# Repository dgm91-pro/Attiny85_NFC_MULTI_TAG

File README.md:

# NFC Profile Keychain

See [`HACKCLUB_REQUEST.md`](HACKCLUB_REQUEST.md) for the message prepared for Hack Club.

A compact, battery-powered NFC keychain built around an **ATtiny85V** and an **ST25DV04KC dynamic NFC tag**. A single button switches between four configurable URL profiles, each indicated by an RGB LED.

> **Project status:** Prototype / under development. The firmware and hardware have not yet been independently verified. Please review the design and test it before relying on it.

## Features

- Four selectable NFC URL profiles: blue, red, green, and violet
- One-button interface
- RGB LED feedback
- NFC is disabled when the device starts and when it is switched off
- Selected profile is saved in the ATtiny85 EEPROM
- Low-power sleep while switched off
- I²C error feedback: four yellow flashes

## How it works

| Action | Result |
|---|---|
| Power-on | The keychain starts with NFC disabled |
| Short press while off | Enables NFC and displays the saved profile |
| Short press while on | Switches to the next profile: blue → red → green → violet |
| Long press (at least 1 second) while on | Disables NFC |
| While on | Brief LED pulse approximately every 4 seconds |
| I²C / NFC error | Four yellow flashes |

The four URL values are currently examples and should be replaced with the intended destinations before testing:

- `URL_0`: blue profile
- `URL_1`: red profile
- `URL_2`: green profile
- `URL_3`: violet profile

The firmware supports `http://` and `https://` URLs and documents a maximum URL length of 116 characters.

## Hardware

The current bill of materials includes:

- **Microcontroller:** ATtiny85V-10SU, 8-pin SOIC
- **NFC tag IC:** ST25DV04KC
- **RGB LED:** Kingbright APTF1616LSEEZGKQBKC, common anode
- **Battery:** CR2032 (3 V)
- **Button:** momentary tactile switch
- Supporting resistors and capacitors

The KiCad project files and a DigiKey parts-list CSV are included in this repository.

## Pin mapping

The mapping below follows the firmware comments and refers to the ATtiny85 SOIC-8 package pin numbers.

| ATtiny85 pin | Signal | Connection |
|---|---|---|
| 1 / PB5 | RESET | ISP header; 10 kΩ pull-up |
| 2 / PB3 | LED green | RGB LED cathode through resistor |
| 3 / PB4 | LED blue | RGB LED cathode through resistor |
| 4 | GND | Ground |
| 5 / PB0 | SDA | ST25DV04KC SDA; 10 kΩ pull-up |
| 6 / PB1 | LED red | RGB LED cathode through resistor |
| 7 / PB2 | SCL / button | ST25DV04KC SCL, 10 kΩ pull-up, button to GND |
| 8 | VCC | 3 V supply |

**Important:** PB2 is shared by I²C SCL and the button. The firmware waits for the button to be released before starting I²C operations.

## Firmware setup

The firmware is in [`program/program.ino`](program/program.ino).

1. Install Arduino IDE 2.x.
2. Install **ATTinyCore** and select the ATtiny85 target.
3. Select the **ATtiny85 (no bootloader)** board option and the internal 1 MHz clock.
4. Select a compatible ISP programmer, such as USBasp. The original notes specify the programmer's **SLOW** setting for a 1 MHz target.
5. Burn the bootloader / initialization sequence once to configure the fuses, if required by your setup.
6. Replace the example URLs in `program.ino`.
7. Remove the CR2032 before programming. Power the board from a suitable programmer or regulated supply set to the correct voltage, and upload using **Sketch → Upload Using Programmer**.

Menu labels can vary with Arduino IDE and ATTinyCore versions; confirm the target, clock, and fuse settings for your exact setup.

## Safety and testing notes

- **Remove the CR2032 before connecting a programmer or external power supply.** Never connect a battery to an external supply at the same time.
- Keep all programming signals within the ATtiny85's and NFC IC's supported voltage limits. Do not apply 5 V logic to a circuit designed for a 3 V supply.
- Verify the schematic, PCB footprint assignments, power connections, pull-ups, and LED polarity before assembling the board.
- Test the NFC behavior with a compatible NFC phone or reader and confirm that each profile opens the expected URL.
- The current repository has not been confirmed to compile or to work on physical hardware. A review and hardware test are still needed.

## Repository layout

```text
.
├── Budget/
│   ├── HackClub-8pin.csv
│   └── OSH-Park.png
├── KiCad/
│   ├── tag.zip
│   └── IF LIB NOT WORKING.zip
├── program/
│   └── program.ino
├── README.md
└── HACKCLUB_REQUEST.md
```

## Help / review requested

I would appreciate a quick review of the KiCad design and firmware before ordering or assembling the boards. In particular, I would like confirmation that the PCB and component footprints look correct, the ATtiny85/ST25DV04KC wiring is plausible, and the firmware's NFC/I²C behavior is likely to work as intended.

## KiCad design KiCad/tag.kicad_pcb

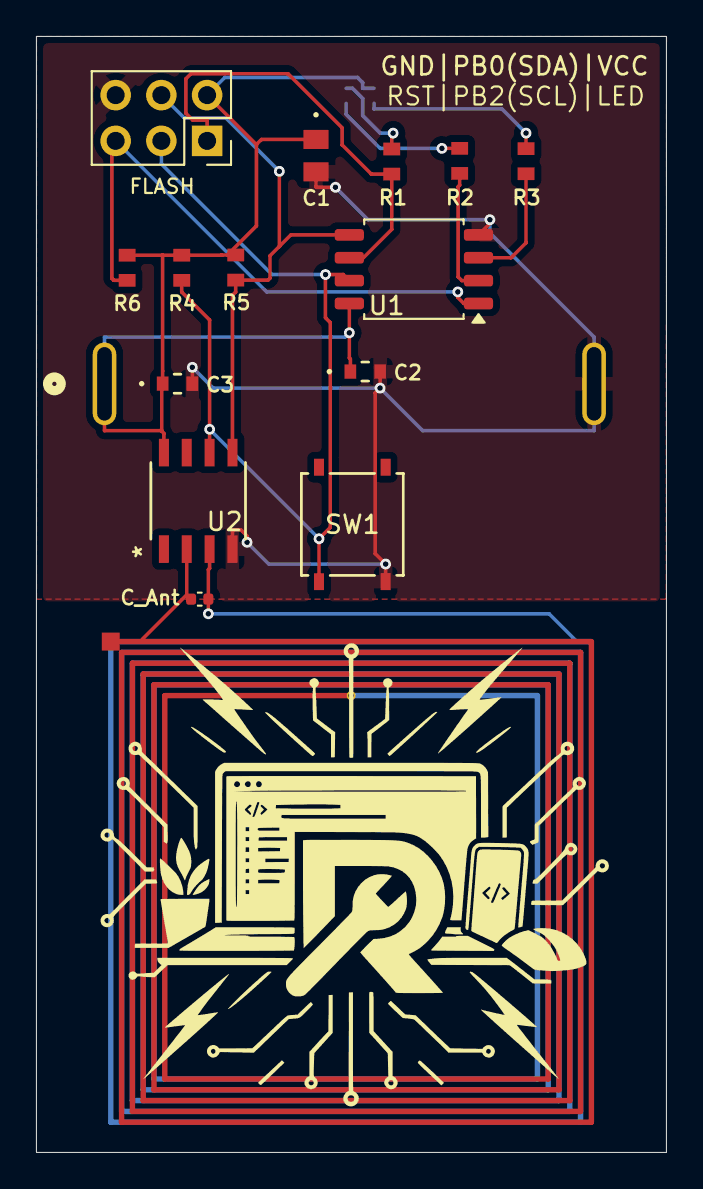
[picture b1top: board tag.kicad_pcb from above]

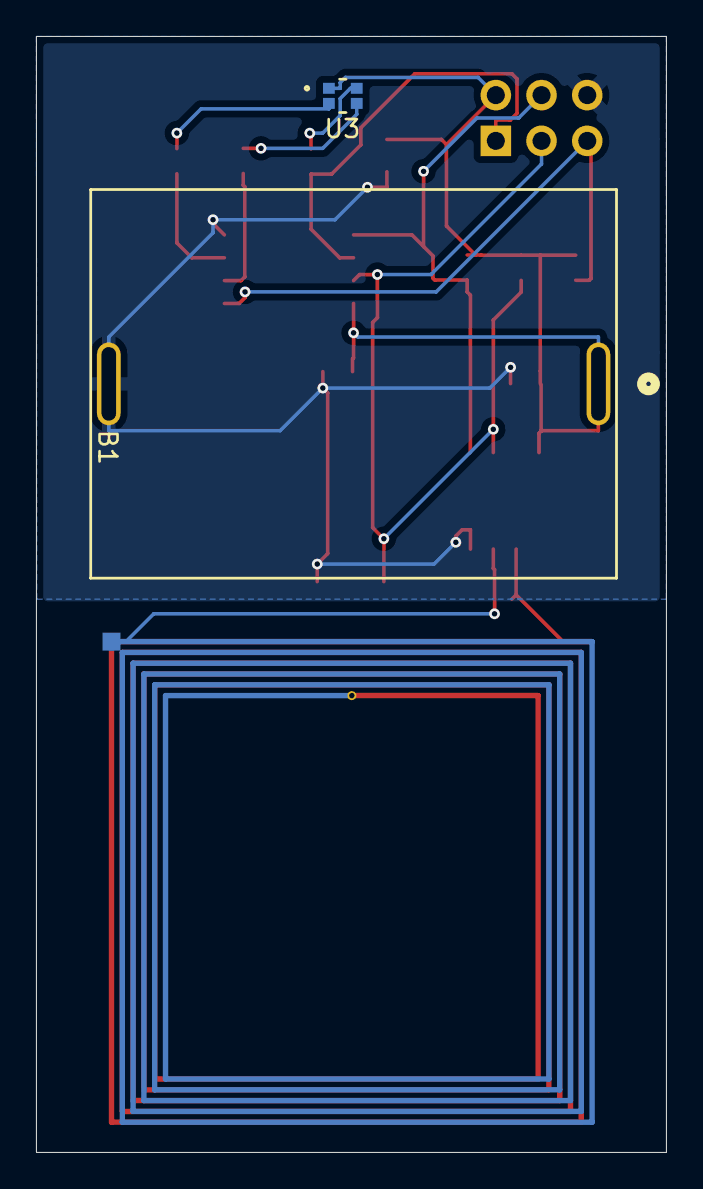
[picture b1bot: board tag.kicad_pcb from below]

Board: 2 copper layers, 35.0 x 62.0 mm, 17 parts (2 on the bottom side), 13 nets.

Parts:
B1: BC2032-E2; BC2032-E2_MPD
C1: CL21B106KOQNNNE; CAP_CL21B106KOQNNNE_SAM
C2, C3: CL10B104KO8NNNC; CAP_CL10_SAM
C_Ant: C; C_0402_1005Metric
FLASH: Conn_02x03_Counter_Clockwise; PinSocket_2x03_P2.54mm_Vertical
L1: L; ANT_Spiral_v3
R1: RMCF0603FT470R; STA_RMCF0603_STP
R2: RMCF0603FT220R; STA_RMCF0603_STP
R3: RMCF0603FT33R0; STA_RMCF0603_STP
R4, R5, R6: RMCF0603FT10K0; STA_RMCF0603_STP
SW1: PTS526 SM15 SMTR2 LFS; SON4_PTS526 SM15 SMTR2 LFS_CNK
U1: ATtiny85V-10S; SOIC-8_5.3x5.3mm_P1.27mm
U2: ST25DV04KC-IE6S3; SO-8_STM
U3: APTF1616LSEEZGKQBKC; SON4_APTF1616LSEEZGKQBKC_KNB_fixed

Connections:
GND: B1.2, C1.2, C2.2, C3.2, FLASH.6, SW1.3, U1.4 (GND), U2.4 (VSS)
unnamed: FLASH.1, R1.1, U1.6 (PB1)
unnamed: FLASH.3, R4.1, SW1.1, U1.7 (PB2), U2.6 (SCL)
unnamed: FLASH.4, R5.1, U1.5 (AREF/PB0), U2.5 (SDA)
unnamed: FLASH.5, R6.2, U1.1 (~RESET/PB5)
unnamed: R2.1, U1.2 (XTAL1/PB3)
unnamed: R3.1, U1.3 (XTAL2/PB4)
unnamed: C_Ant.1, L1.1, U2.2 (AC0)
unnamed: C_Ant.2, L1.2, U2.3 (AC1)
unnamed: R3.2, U3.4 (BLUE)
unnamed: R2.2, U3.3 (GREEN)
unnamed: R1.2, U3.2 (RED)
VCC: B1.1, C1.1, C2.1, C3.1, FLASH.2, R4.2, R5.2, R6.1, U1.8 (VCC), U2.8 (VCC), U3.1 (VCC)

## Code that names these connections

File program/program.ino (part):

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 * Pile : CR2032 (3 V)
 *
 * Brochage ATtiny85 (numero de patte du boitier SOIC-8)
 *   1 PB5 /RESET  -> en-tete ISP uniquement (+ pull-up 10k)
 *   2 PB3         -> LED verte  (cathode, via R)
 *   3 PB4         -> LED bleue  (cathode, via R)
 *   4 GND
 *   5 PB0         -> SDA  (ST25DV patte 5)  + pull-up 10k   [ISP: MOSI]
 *   6 PB1         -> LED rouge  (cathode, via R)            [ISP: MISO]
 *   7 PB2         -> SCL  (ST25DV patte 6)  + pull-up 10k + BOUTON vers GND  [ISP: SCK]
 *   8 VCC
 *
 * Fonctionnement
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static const char *const URLS[4] PROGMEM = { URL_0, URL_1, URL_2, URL_3 };

/* ---- broches ---- */
#define K_SDA   PB0
#define K_SCL   PB2          /* partagee avec le bouton */
#define K_LR    PB1
#define K_LG    PB3
#define K_LB    PB4
#define LED_ALL (_BV(K_LR) | _BV(K_LG) | _BV(K_LB))

/* couleur de chaque profil (broches LED a mettre a 0 V) */
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  led(0);
  DDRB &= (uint8_t)~(_BV(K_SDA) | _BV(K_SCL));  /* bus libere */
  GIFR  = _BV(PCIF);
  PCMSK = _BV(PCINT2);                          /* bouton sur PB2 */
  GIMSK |= _BV(PCIE);
  set_sleep_mode(SLEEP_MODE_PWR_DOWN);
  cli();
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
